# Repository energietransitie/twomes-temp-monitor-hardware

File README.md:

# Twomes Temperature Monitor Hardware

This repository contains the open hardware design files for the battery powered Twomes Temperature Monitor hardware, which can read measurement data from a varity of sensors:
* two [DS18b20(Z)](https://www.maximintegrated.com/en/products/sensors/DS18B20.html) temperature sensors in clamps that can be connected the supply water pipe (from the boiler to the hydronic radiators) and return water pipe (from the hydronic radiators to the boiler);
* an [Si7051](https://www.silabs.com/sensors/temperature/si705x/device.si7051) sensor mounted 
on the main PCB itself to measure room temperature;
* a [Twomes CO₂ Monitor Shield](https://github.com/energietransitie/twomes-co2-monitor-hardware) with the [WeMos D1 Mini shield](https://www.wemos.cc/en/latest/d1_mini_shield/index.html) form factor that measures temperature via an [Si7051](https://www.silabs.com/sensors/temperature/si705x/device.si7051) sensor and a Sensirion [SCD41](https://www.sensirion.com/en/environmental-sensors/carbon-dioxide-sensors/carbon-dioxide-sensor-scd4x/) sensor that measures CO₂ concentration, relative humidity and temperatue;
* a [SEK-SCD41](https://www.sensirion.com/en/environmental-sensors/evaluation-kit-sek-environmental-sensing/evaluation-kit-sek-scd41/) evaluation board that that measures CO₂ concentration, relative humidity and temperature.

The Twomes Temperature Monitor hardware can wirelessly send data to the [Twomes P1 Gateway measurement device](https://github.com/energietransitie/twomes-p1-gateway-firmware) using [ESP-NOW](https://www.espressif.com/en/products/software/esp-now/overview).

## Table of contents
* [General info](#general-info)
* [Producing](#producing)
* [Developing](#developing) 
* [Features](#features)
* [Status](#status)
* [License](#license)
* [Citation](#citation)
* [Credits](#credits)

## General info
This repository contains the the source files and fabrication files of the hardware designs of theTwomes Room Monitor and Twomes Boiler Monitor pcb and its enclosure. It also includes a `docs` folder with recent printouts of the [schematics](./docs/twomes-temp-monitor-hardware-sch.pdf) and [PCB layout](./docs/twomes-temp-monitor-hardware-pcb.pdf). 

For the associated firmwware that you can run on this hardware, please see the following repositories:
* [twomes-twomes-room-monitor-firmware](https://github.com/energietransitie/twomes-room-monitor-firmware);
* [twomes-twomes-boiler-monitor-firmware](https://github.com/energietransitie/twomes-boiler-monitor-firmware);

## Producing
### Printed Circuit Board
To fabricate the printed circuit board you can use various PCB services. 

The folder [pcb/jlcpcb](./pcb/jlcpcb) includes all exported files needed to have the PCBs manufactured by [JLCPCB](https://www.jlcpcb.com). 
Upload the [zipped gerber files](./pcb\jlcpcb\gerber\gerber-TwomesSensor.zip) to the [JLCPCB quote page](https://cart.jlcpcb.com/quote), select the amount of PCBs and a colour for the silkscreen. All other options can be left on default. If SMT assembly is desired, also select this option before ordering. This will take you to a page where the BOM and POS file can be uploaded.  

Assembly of components depends on the variant you need:
* for assembly of a Twomes Boiler Monitor PCB, use the files [BOM-TwomesBoilerSensor.csv](./pcb/jlcpcb/assembly/boiler-monitor/BOM-TwomesBoilerSensor.csv) and [CPL-TwomesBoilerSensor.csv](./pcb/jlcpcb/assembly/boiler-monitor/CPL-TwomesBoilerSensor.csv);
* for assembly of a Twomes Room Monitor PCB, use the files [BOM-TwomesRoomSensor.csv](./pcb/jlcpcb/assembly/room-monitor/BOM-TwomesRoomSensor.csv) and [CPL-TwomesRoomSensor.csv](./pcb/jlcpcb/assembly/room-monitor/CPL-TwomesRoomSensor.csv)

N.B. All components marked "DO NOT PLACE" in the BOM-*.csv files can not be ordered from JLCPCB and need to be ordered from other services and placed manually.

### Enclosure
To fabricate the boiler monitor enclosure or the room room monitor enclosure you can use your own 3D printer or use a 3D printing service. 

Below you find a photo of the boiler enclosure. 

The folder [enclosure/fabrication](./enclosure/fabrication) contains exported STL files. You can print two types of enclusure:
* all enclusures share the same [case](./enclosure/fabrication/twomes-temp-monitor-enclosure-case.stl) and one [button](./enclosure/fabrication/twomes-temp-monitor-enclosure-button.stl)
* for a Twomes Boiler Monitor you need a [boiler monitor lid](./enclosure/fabrication/twomes-boiler-monitor-enclosure-lid.stl) and two [sensor clamps](./enclosure/fabrication/twomes-boiler-monitor-enclosure-clamp.stl); 
* for a Twomes Room Monitor you need a [room monitor lid](./enclosure/fabrication/twomes-room-monitor-enclosure-lid.stl).

The STL files can be imported into any slicer and turned into G-Code for a 3D printer. You can also upload the STL files to an online 3D printing service of your choice.

## Developing

### Printed Circuit Board
To change the hardware design of the PCB, you need:
* [KiCad](https://www.kicad.org/download/) installed to change te PCB design. 

The KiCad source files of the PCB can be found in the folder [pcb](./pcb).

To convert the PCBs into a format suitable for fabrication, consult the webpage of your PCB manufacturer of choice. For example, see the [JLCPCB guide on how to export Gerbers](https://support.jlcpcb.com/article/149-how-to-generate-gerber-and-drill-files-in-kicad) and the  [JLCPCB guide how to export the BOM and POS files](https://support.jlcpcb.com/article/84-how-to-generate-the-bom-and-centroid-file-from-kicad). You may also use a KiCad plug-in for this purpose such as [kicad-jlcpcb-tools](https://github.com/Bouni/kicad-jlcpcb-tools).

### Enclosure
To change the hardware design of the enclosure, you need either:
* [Autodesk Fusion 360](https://www.kicad.org/download/) installed (Autodesk provides 30 day free trials and [free one-year educational access](https://www.autodesk.com/education/edu-software/overview?sorting=featured&filters=individual) to its products and services for eligible students, teachers and research staff); 
* or [FreeCAD](https://www.freecadweb.org/), an open source alternative.

The source files of the enclosure can be found in the folder [enclosure](./enclosure). We include both .f3d source files and .step source files we obtained after conversion.
## Features
The Twomes Temperature Monitor device features the follwoing main hardware components:
* [ESP32-WROOM-32E](https://www.espressif.com/sites/default/files/documentation/esp32-wroom-32e_esp32-wroom-32ue_datasheet_en.pdf) module;
* supercapacitor to assist the battery in high-current bursts.
* battery holder for a 3.6 V AA-size battery, such as the SAFT LS14500 Lithium Thionyl battery.
* FTDI compatible serial programming header (3.3 V).

To-do:
* remove `SW2` (not used in newer firmware)
* remove holes above SW2 and SW3 in enclosure lids (SW3 not used in newer firmware; SW2 does not need to be user accessible, only used during deployment))  
* remove letters 'R' and 'K' from enclusure lids (only a single end-user accessible button used in newer firmware )
## Status
Project is: _in progress_

## License
The hardware designs in this repository are available under the [CERN-OHL-P v2 license](./LICENSE), Copyright 2022 [Research group Energy Transition, Windesheim University of Applied Sciences](https://windesheim.nl/energietransitie)

## Citation

If you use this repository in your research or work, please cite the following pre-print, which describes the overall NeedForHeat DataGear system of which this repository is a part:

> Ter Hofte, H., & van Ravenzwaaij, N. (2025). *NeedForHeat DataGear: An Open Monitoring System to Accelerate the Residential Heating Transition*. arXiv preprint arXiv:2509.06927. https://doi.org/10.48550/arXiv.2509.06927

**Note:** This is a pre-print submitted on 8 Sep 2025 and has not yet been peer-reviewed. For the full paper, see [https://arxiv.org/abs/2509.06927](https://arxiv.org/abs/2509.06927).

## Credits
This open hardware design is made by:
* Sjors Smit · [@Shorts1999](https://github.com/Shorts1999)

Thanks also go to:
* Fredrik-Otto Lautenbag ·  [@Fredrik1997](https://github.com/Fredrik1997)
* Gerwin Buma ·  [@GerwinBuma](https://github.com/GerwinBuma) 
* Marco Winkelman · [@MarcoW71](https://github.com/MarcoW71)

Product owner:
* Marco Winkelman · [@MarcoW71](https://github.com/MarcoW71)

We use and gratefully acknowlegde the efforts of the makers of the following designs:
* [KiCad Libraries](https://kicad.github.io/), by the KiCad Development Team, licensed under [an adapted version of the CC-BY-SA 4.0 License](https://www.kicad.org/libraries/license/)

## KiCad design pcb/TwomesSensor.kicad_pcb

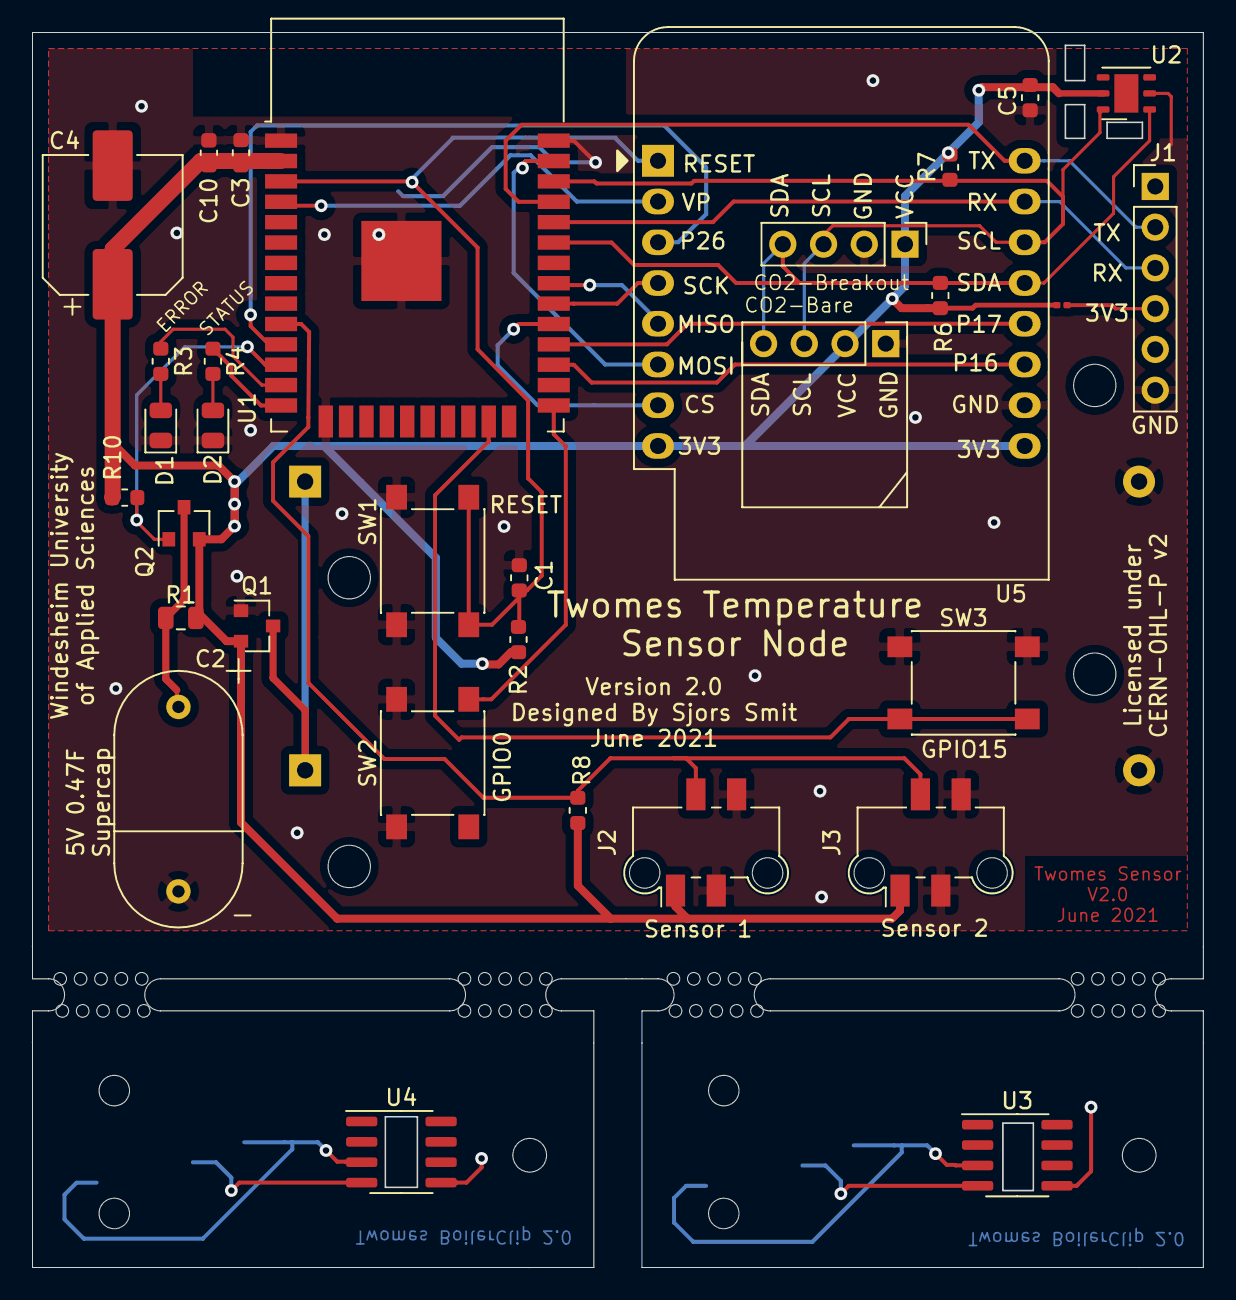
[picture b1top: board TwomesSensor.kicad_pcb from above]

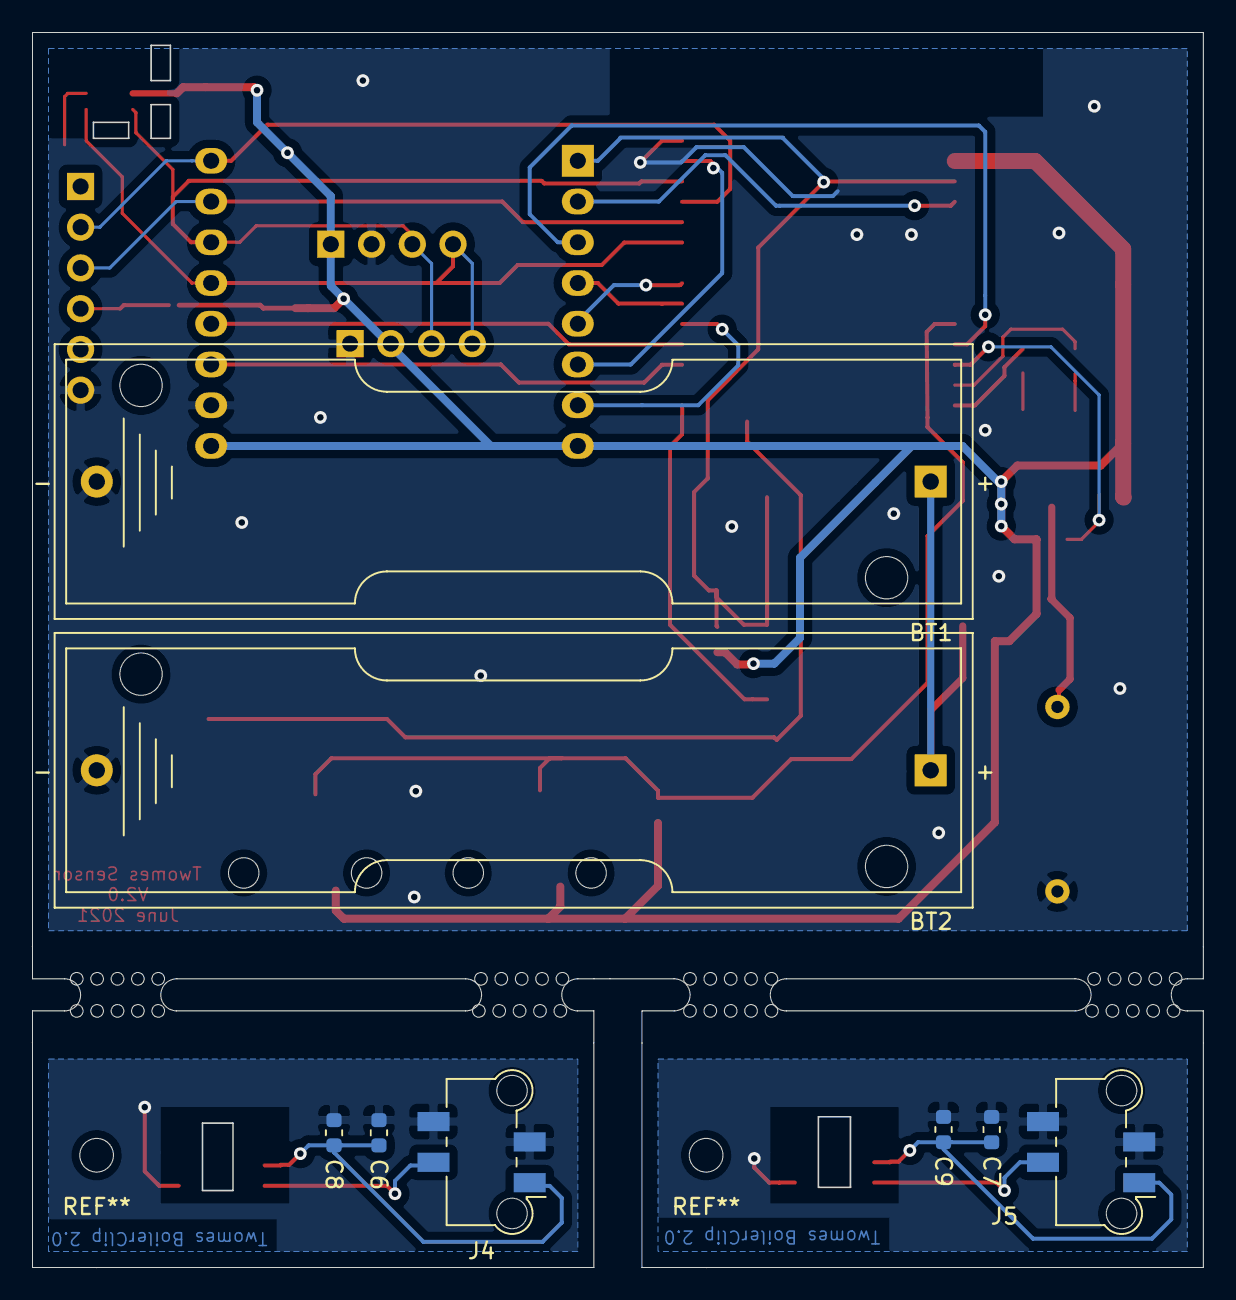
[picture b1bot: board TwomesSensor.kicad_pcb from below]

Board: 2 copper layers, 73.0 x 77.0 mm, 40 parts (8 on the bottom side), 32 nets.

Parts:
BT1, BT2: LS14500; BatteryHolder_Keystone_2460_1xAA
C1, C6, C7: 1uF; C_0603_1608Metric
C2: 0.47F; Supercap-Dual-5V-8x16
C3, C5, C8, C9: 100nF; C_0603_1608Metric
C4: 470uF; CP_Elec_8x10.5
C10: 10uF; C_0603_1608Metric
CO2-Bare, CO2-Breakout: Conn_01x04_Female; PinHeader_1x04_P2.54mm_Vertical
D1: RED_LED; LED_0805_2012Metric
D2: GREEN_LED; LED_0805_2012Metric
J1: Female header; PinHeader_1x06_P2.54mm_Vertical
J2, J3, J4, J5: Molex PicoFlex 90814; Molex_Picoflex_90814-0004_2x02_P1.27mm_Vertical
JP1: SolderJumper; R_0201_0603Metric
Q1, Q2: PMV48XP,215; SOT-23
R1: 100R; R_0805_2012Metric
R2: 10K; R_0603_1608Metric
R3, R4: 1K; R_0603_1608Metric
R6, R7, R10: 10k; R_0603_1608Metric
R8: 4k7; R_0603_1608Metric
SW1, SW2, SW3: SW_Push; SW_Push_1P1T_NO_6x6mm_H9.5mm
U1: ESP32-WROOM-32D; ESP32-WROOM-32
U2: Si7051-A20; DFN-6-1EP_3x3mm_P1mm_EP1.5x2.4mm
U3, U4: DS18B20Z; SOIC-8_3.9x4.9mm_P1.27mm
U5: WeMos_D1_mini_breakout; WEMOS_D1_mini_light

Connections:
+BATT: BT1.1, BT2.1, Q1.3
/BUTTON: SW3.2, U1.23
/ESP_CS: U1.29, U5.7
/ESP_MISO: U1.31, U5.5
/ESP_MOSI: U1.37, U5.6
/ESP_SCK: U1.30, U5.4
/ESP_SCL: CO2-Bare.3, CO2-Breakout.3, R7.1, U1.36, U2.6, U5.14
/ESP_SDA: CO2-Bare.4, CO2-Breakout.4, R6.1, U1.33, U2.1, U5.13
/GPIO0: SW2.2, U1.25
/GPIO16: U1.27, U5.11
/GPIO17: U1.28, U5.12
/LED_ERROR: R3.1, U1.13
/LED_STATUS: R4.1, U1.14
/OneWire_Bus: J2.2, J3.2, R8.1, U1.10
/RX0: J1.3, U1.34, U5.15
/Reset: C1.1, R2.2, SW1.2, U1.3, U5.1
/SwitchCap: Q2.1, R10.2, U1.12
/TX0: J1.2, U1.35, U5.16
/Temp1GND: C7.2, C9.2, J5.3, J5.4, U4.5
/Temp1VCC: C7.1, C9.1, J5.1, U4.3
/Temp2GND: C6.2, C8.2, J4.3, J4.4, U3.5
/Temp2VCC: C6.1, C8.1, J4.1, U3.3
/WEMOS_A0: U1.4, U5.2
/WEMOS_D0: U1.11, U5.3
GND: BT1.2, BT2.2, C1.2, C2.2, C3.2, C4.2, C5.2, C10.2, CO2-Bare.1, CO2-Breakout.2, D1.1, D2.1, J1.6, J2.3, J2.4, J3.3, J3.4, Q1.1, SW1.1, SW2.1, SW3.1, U1.1, U1.15, U1.38, U1.39, U2.2, U5.10
unnamed: C2.1, Q2.3, R1.1
unnamed: D1.2, R3.2
unnamed: D2.2, R4.2
unnamed: J1.4, JP1.1
unnamed: J4.2, U3.4
unnamed: J5.2, U4.4
VCC: C3.1, C4.1, C5.1, C10.1, CO2-Bare.2, CO2-Breakout.1, J2.1, J3.1, JP1.2, Q1.2, Q2.2, R1.2, R2.1, R6.2, R7.2, R8.2, R10.1, U1.2, U2.5, U5.8, U5.9

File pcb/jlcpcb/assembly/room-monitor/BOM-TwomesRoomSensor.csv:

Comment,Designator,Footprint,LCSC
LS14500,"BT1,BT2",Battery:BatteryHolder_Keystone_2460_1xAA,DO NOT PLACE
1uF,"C1,C6,C7",Capacitor_SMD:C_0603_1608Metric,C15849
0.47F,C2,SuperCap,DO NOT PLACE
470uF,C4,Capacitor_SMD:CP_Elec_8x10.5,C141429
100nF,"C3,C5,C8,C9",Capacitor_SMD:C_0603_1608Metric,C14663
10uF,C10,Capacitor_SMD:C_0603_1608Metric,C19702
RED_LED,D1,LED_SMD:LED_0805_2012Metric,C84256
GREEN_LED,D2,LED_SMD:LED_0805_2012Metric,C2297
Female header,J1,Connector_PinHeader_2.54mm:PinHeader_1x06_P2.54mm_Vertical,DO NOT PLACE
Molex PicoFlex 90814,"J2,J3,J4,J5",Connector_Molex:Molex_Picoflex_90814-0004_2x02_P1.27mm_Vertical,DO NOT PLACE
SolderJumper,JP1,Resistor_SMD:R_0201_0603Metric,DO NOT PLACE
"PMV48XP,215","Q1,Q2",Package_TO_SOT_SMD:SOT-23,C75560
100R,R1,Resistor_SMD:R_0805_1608Metric,C17408
10K,R2,Resistor_SMD:R_0603_1608Metric,C25804
1K,"R3,R4",Resistor_SMD:R_0603_1608Metric,C21190
10k,"R6,R7,R10",Resistor_SMD:R_0603_1608Metric,C25804
4k7,R8,Resistor_SMD:R_0603_1608Metric,C23162
SW_Push,"SW1,SW2,SW3",Button_Switch_SMD:SW_Push_1P1T_NO_6x6mm_H9.5mm,C83206
ESP32-WROOM-32E,U1,RF_Module:ESP32-WROOM-32,C701343
Si7051-A20,U2,Package_DFN_QFN:DFN-6-1EP_3x3mm_P0.95mm_EP1.7x2.6mm,DO NOT PLACE
DS18B20Z,"U3,U4",Package_SO:SOIC-8_3.9x4.9mm_P1.27mm,C97190
WeMos_D1_mini_breakout,U5,Module:WEMOS_D1_mini_light_shield-Breakout,DO NOT PLACE

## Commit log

2021-06-29 Update CO2 sensor footprint
2021-07-09 Update README.md
    updated to match repo renames and to aligned with other repo descriptions
2021-11-12 Update to new Directory format/name
2021-11-12 New enclosures with correct slots and new letter names
2021-12-29 directory restructure
2021-12-30 Update README.md
    make consistent with other hardware repo readme
2021-12-30 fix typos
2022-01-04 update image
2022-01-04 fix based on review other repo
2022-01-06 restructured repo and updated README
2022-01-06 Seperate BOM for Boiler and Room sensor
    Only change in components is:
    Si7051 for room placed, DS18B20 not placed
    DS18B20 placed on room, not on boiler
    All other components marked as "DO NOT PLACE" can not be ordered from JLCPCB and need to be ordered and placed manually from other services
2022-01-06 add sources for clamps
2022-01-06 different assembly instructions for room monitor
2022-01-06 add info about DO NOT PLACE designator
2022-01-06 fix typo
2022-01-07 update CO2 monitor hardware name
2022-04-01 Update README.md
    updates ESP32 module that was actually used
2022-04-07 Update README.md
    Repaired reference URL to CO2 Monitor Shield hardware
